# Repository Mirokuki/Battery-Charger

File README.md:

# 6-slot 1S / 2S USB-C LiPo balance charger

A USB-C powered charger with six independent slots. Every slot takes either a
1S pack (PicoBlade, e.g. Blade Nano 150 mAh) or a 2S pack (XT30 plus its JST-XH
balance lead, e.g. Mobula8 350 mAh). It works out which one is plugged in and
charges it at the voltage and rate you set on a small OLED with three buttons.
2S packs are balanced while they charge, and both cell voltages are shown.

**Status: design files generated, nothing built or powered yet.** See
[Before you order](#before-you-order).

## How it works

```
USB-C ── AP33771C (asks the adapter for 9 V) ── VBUS ─┬─ AP63203 buck ── 3.3 V ── ESP32-C3, OLED, I2C mux
                                                     └─ 6 x BQ25798 buck-boost charger (one per slot)

slot:  BQ25798 BAT ──┬── P-FET pair ── PicoBlade (1S)      switch driven by the charger's D+ pin
                     └── P-FET pair ── XT30 (2S)           switch driven by the charger's D- pin
       JST-XH balance port ─┬─ BQ29209 balancer ── over-voltage flag ── charger TS pin
                            └─ 1 M dividers ── ADS1115 ADC (one per two slots) ── cell voltages
```

- **Any slot, either battery.** The BQ25798 is a buck-boost charger that is
  switched between 1S and 2S over I2C, so it also works from a plain 5 V port.
- **Detection.** With charging off, the firmware empties the charger's output
  node, closes one connector's switch and reads the pack voltage with the
  charger's own ADC, then does the same for the other connector.
  - PicoBlade 2.5–4.45 V → 1S, starts charging
  - XT30 5.0–8.9 V → 2S, starts charging
  - XT30 2.5–4.45 V → could be a 1S pack or a flat 2S: asks you to confirm
  - both connectors live → fault, nothing is charged
- **The two power connectors of a slot can never be joined.** Each has its own
  back-to-back P-FET pair, off by default, and the firmware closes one at a time.
  A reverse-polarity pack cannot turn its switch on.
- **Balancing.** Each slot's JST-XH port feeds a BQ29209, which compares the
  two cells and bleeds the higher one (about 10 mA) until they match. It starts
  when the cells differ by about 30 mV and needs no firmware. It keeps working
  after the charge finishes for as long as the balance lead is plugged in.
- **Cell voltages.** Precision dividers on each balance port feed three
  ADS1115 16-bit ADCs, so the display shows both cells of a 2S pack
  (`4.12/4.15`). While charging, the firmware stops the slot if a cell goes
  more than 80 mV over the target (`cell high`), in LiHV mode too.
- **Per-cell over-voltage cut-off.** If either cell passes 4.30 V the balancer
  pulls the charger's TS pin low, which stops charging in hardware; the display
  shows `cell>4.3`. The cut-off is ignored in LiHV mode, where 4.35 V per cell
  is the target.
- **Fail-safe.** Charge-enable is pulled off in hardware, so a reset or crashed
  MCU stops all charging. The chargers' own over-voltage protection and 5 h
  safety timer stay active.
- **Power sharing.** The Samsung 25 W adapter gives about 20 W at 9 V. Six 2S
  350 mAh packs at 1C need about 18 W. If you ask for more than the adapter
  has, the firmware scales every slot down by the same factor, and each charger
  also backs off by itself if the input voltage sags.

### Limits you should know about

- **Balancing is gentle.** At about 10 mA it corrects roughly 10 mAh per
  hour, which suits packs that are slightly out, not badly unbalanced ones.
  The balancer runs by itself; the firmware watches the cells but does not
  steer it.
- **A forgotten balance lead is not blocked.** A 2S pack on the XT30 alone
  still charges, unbalanced and without any per-cell protection. You can tell
  from the display: it shows one pack voltage instead of two cell voltages.
- **Cell readings are good to about 10 mV** with the 0.1 % divider resistors
  in the BOM. With 1 % parts expect up to about 40 mV of error.
- **Small packs stop a little early.** The charger chip's lowest termination
  current is 40 mA. For 150 mAh packs the firmware adds a 15 minute top-off,
  but expect roughly 95 % rather than a full 100 %.
- **LiPo vs LiHV cannot be detected**, so it is a per-slot setting (default
  4.20 V, which is safe for both).
- "Storage" only charges up to 3.85 V/cell. It cannot discharge a fuller pack.
- Charge rate is 50–1000 mA per slot in 10 mA steps. Current accuracy near the
  bottom of that range is modest (the chip is a 5 A design).

## Using it

2S: plug in the balance lead and the XT30. 1S: plug into the PicoBlade.

Each slot has one line on the main screen. A 2S pack with its balance lead
shows `2S 4.12/4.15` (cell 1 / cell 2) and the charge current; a balance lead
on its own shows `bal 4.12/4.15`, which makes the charger a quick cell checker.

| Button | Main screen | Slot menu |
|---|---|---|
| UP / DN | pick a slot | move, or change a value while editing |
| OK | open the slot menu | edit / confirm / run the item |

Slot menu: 1S voltage, 1S rate, 2S voltage, 2S rate, Start/Stop, Back. Settings
are remembered per slot. Defaults are 150 mA for 1S and 350 mA for 2S. The green
LED under each slot is on while that slot charges.

Hold **OK** while plugging in USB to put the ESP32 into download mode.

## Files

| Path | What |
|---|---|
| `hardware/design.py` | The circuit: every part, value, order code and net. Edit this, then regenerate. |
| `hardware/gen_schematic.py` | Writes the KiCad schematic (`lipo-charger.kicad_sch`, `slot1..6.kicad_sch`). |
| `hardware/gen_pcb.py` | Places and routes the 108 x 80 mm 4-layer board (`lipo-charger.kicad_pcb`). |
| `hardware/make_outputs.py` | Gerbers, drill, BOM, pick-and-place, schematic PDF, DRC/ERC reports. |
| `hardware/render_copper.py` | Quick picture of the routed copper (`docs/copper.png`). |
| `fab/` | What you upload to JLCPCB. |
| `firmware/lipo_charger/` | Arduino sketch for the ESP32-C3. |
| `case/make_case.py` | Generates `case_base.stl` and `case_lid.stl`. |
| `docs/` | Schematic PDF and board renders. |

Regenerate everything:

```
python hardware/gen_schematic.py
"C:\Program Files\KiCad\10.0\bin\python.exe" hardware/gen_pcb.py
python hardware/make_outputs.py
python case/make_case.py
```

The schematic uses a net label on every pin instead of drawn wires. It is
generated from `design.py` and checked against it, so it is exact, but it reads
like a netlist rather than a hand-drawn schematic.

## Ordering the board (JLCPCB)

- Upload `fab/lipo-charger-gerbers.zip`: 4 layers, 1.6 mm, 1 oz.
- SMT assembly, top side only: `fab/BOM_JLCPCB.csv` and `fab/CPL_JLCPCB.csv`.
  Every surface-mount part is on the top; the bottom carries only copper.
- Rows in the BOM with an empty LCSC number need to be matched by MPN in
  JLCPCB's parts search. The LCSC numbers that are filled in were entered from
  memory and **must be checked** against the part description when you upload.
- Check part rotations in JLCPCB's placement preview, especially the BQ25798,
  the BQ29209, the ADS1115s, the SOT-23 FETs, the LEDs and the ESP32 module.

Hand-soldered after delivery: 6 x XT30UPB-M, 6 x JST B3B-XH-A, 6 x PicoBlade
53047-0210, the OLED module on J2. J3 (UART) is optional.

The OLED is a 0.96" SSD1306 I2C module with pins in the order **GND VCC SCL
SDA**. Some modules swap GND and VCC: check yours against the silkscreen. Solder
it on a plain pin header (not a socket) so the glass sits about 5.5 mm above the
board, hanging towards the front edge.

Buttons need the tall version (PTS645, 9.5 mm) to reach through the lid.

## Firmware

Arduino IDE, board **ESP32C3 Dev Module**, *USB CDC On Boot: Enabled*.
Libraries: Adafruit GFX, Adafruit SSD1306. Flash over the USB-C port.

## Case

Outside size 112.8 x 84.8 x 14.8 mm. `case_base.stl` prints as is,
`case_lid.stl` is already flipped to print top-face down. No supports.

Hardware: 4 x M3 heat-set insert (5.0 mm knurl, 4.2 mm pilot, 4.0 mm long) and
4 x M3 x 8 socket-head screw.

1. Melt an insert into the open end of each of the four lid posts, flush with
   the end of the post.
2. Drop the board into the base. It rests on the four bosses and seven pegs.
3. Fit the lid. The posts land on the board around its M3 holes.
4. Screw in from underneath. The heads sit in 6.2 x 3.2 mm recesses, so the
   case sits flat, and the top of the lid has no screw holes.

The opening sizes, insert hole (`INSERT_HOLE`, 4.2 mm) and screw recess are
parameters at the top of `case/make_case.py`. Print one post as a test before
committing to the insert hole size for your filament. The OLED window position
(`OLED_WIN`) depends on the module, so measure yours first.

## Before you order

Nothing here has been built. Do these first:

1. **Open the board in KiCad and look it over.** It was placed and routed by
   script. Rule-check results are in the section below.
2. **PicoBlade polarity.** Pin 1 (the pad nearer the balance port) is positive,
   pin 2 is ground. Check with a meter that this matches your Blade packs. A
   reversed pack is simply not detected, so a wrong guess shows up as "nothing
   happens", not damage.
3. **Balance port pinout.** Pin 1 (square pad, at the left) is pack negative,
   pin 2 the cell junction, pin 3 pack positive, which is the usual JST-XH
   balance wiring. Check one of your packs with a meter.
4. **The D+/D- switch drive is unusual.** The BQ25798 documents its D+/D-
   pins as host-programmable 0–3.3 V outputs (register 0x47), and this design
   uses them to drive the FET gate drivers. The datasheet does not state how
   much current they source; the load here is 49 µA. Worth proving on one slot
   before populating all six.
5. **Order the BQ29209, not the BQ29200.** The two share a datasheet; the
   BQ29209 trips at 4.30 V per cell, the BQ29200 at 4.35 V.
6. **First power-up without batteries**, on a current-limited supply if you
   have one. All six slots should report `--`. Then try one pack with a meter
   on it and compare voltage and current with the display.
7. **Compile the firmware.** It has not been compiled or run.
8. Never leave charging packs unattended, especially on an unproven charger.

## Rule-check results

From the last run on 2026-11-11 (KiCad 10.0, `hardware/make_outputs.py`):

| Check | Result |
|---|---|
| Schematic netlist vs `design.py` | 397 of 397 parts, 0 net mismatches |
| Board vs schematic (parity) | 0 issues |
| Board DRC errors | 0 |
| Unconnected nets | 0 |
| Board DRC warnings | 9: seven unused escape vias on I2C lines, two silkscreen lines of the ESP32 module at the board edge |
| Schematic ERC | 3 "power pin not driven" (the schematic has no power-flag symbols) and 7 library notes about generated symbols. No wiring faults. |
| Case meshes | both STLs closed (every edge shared by exactly two faces) |

Board rules used: 0.127 mm clearance, 0.15 mm minimum track, 0.6/0.3 mm vias,
0.2 mm minimum hole (the ESP32 footprint's thermal vias), 0.18 mm hole clearance
(the USB-C footprint's own locating holes sit 0.194 mm from its pads).

DRC proves the copper matches the netlist and meets spacing rules. It does not
prove the circuit works: see "Before you order".

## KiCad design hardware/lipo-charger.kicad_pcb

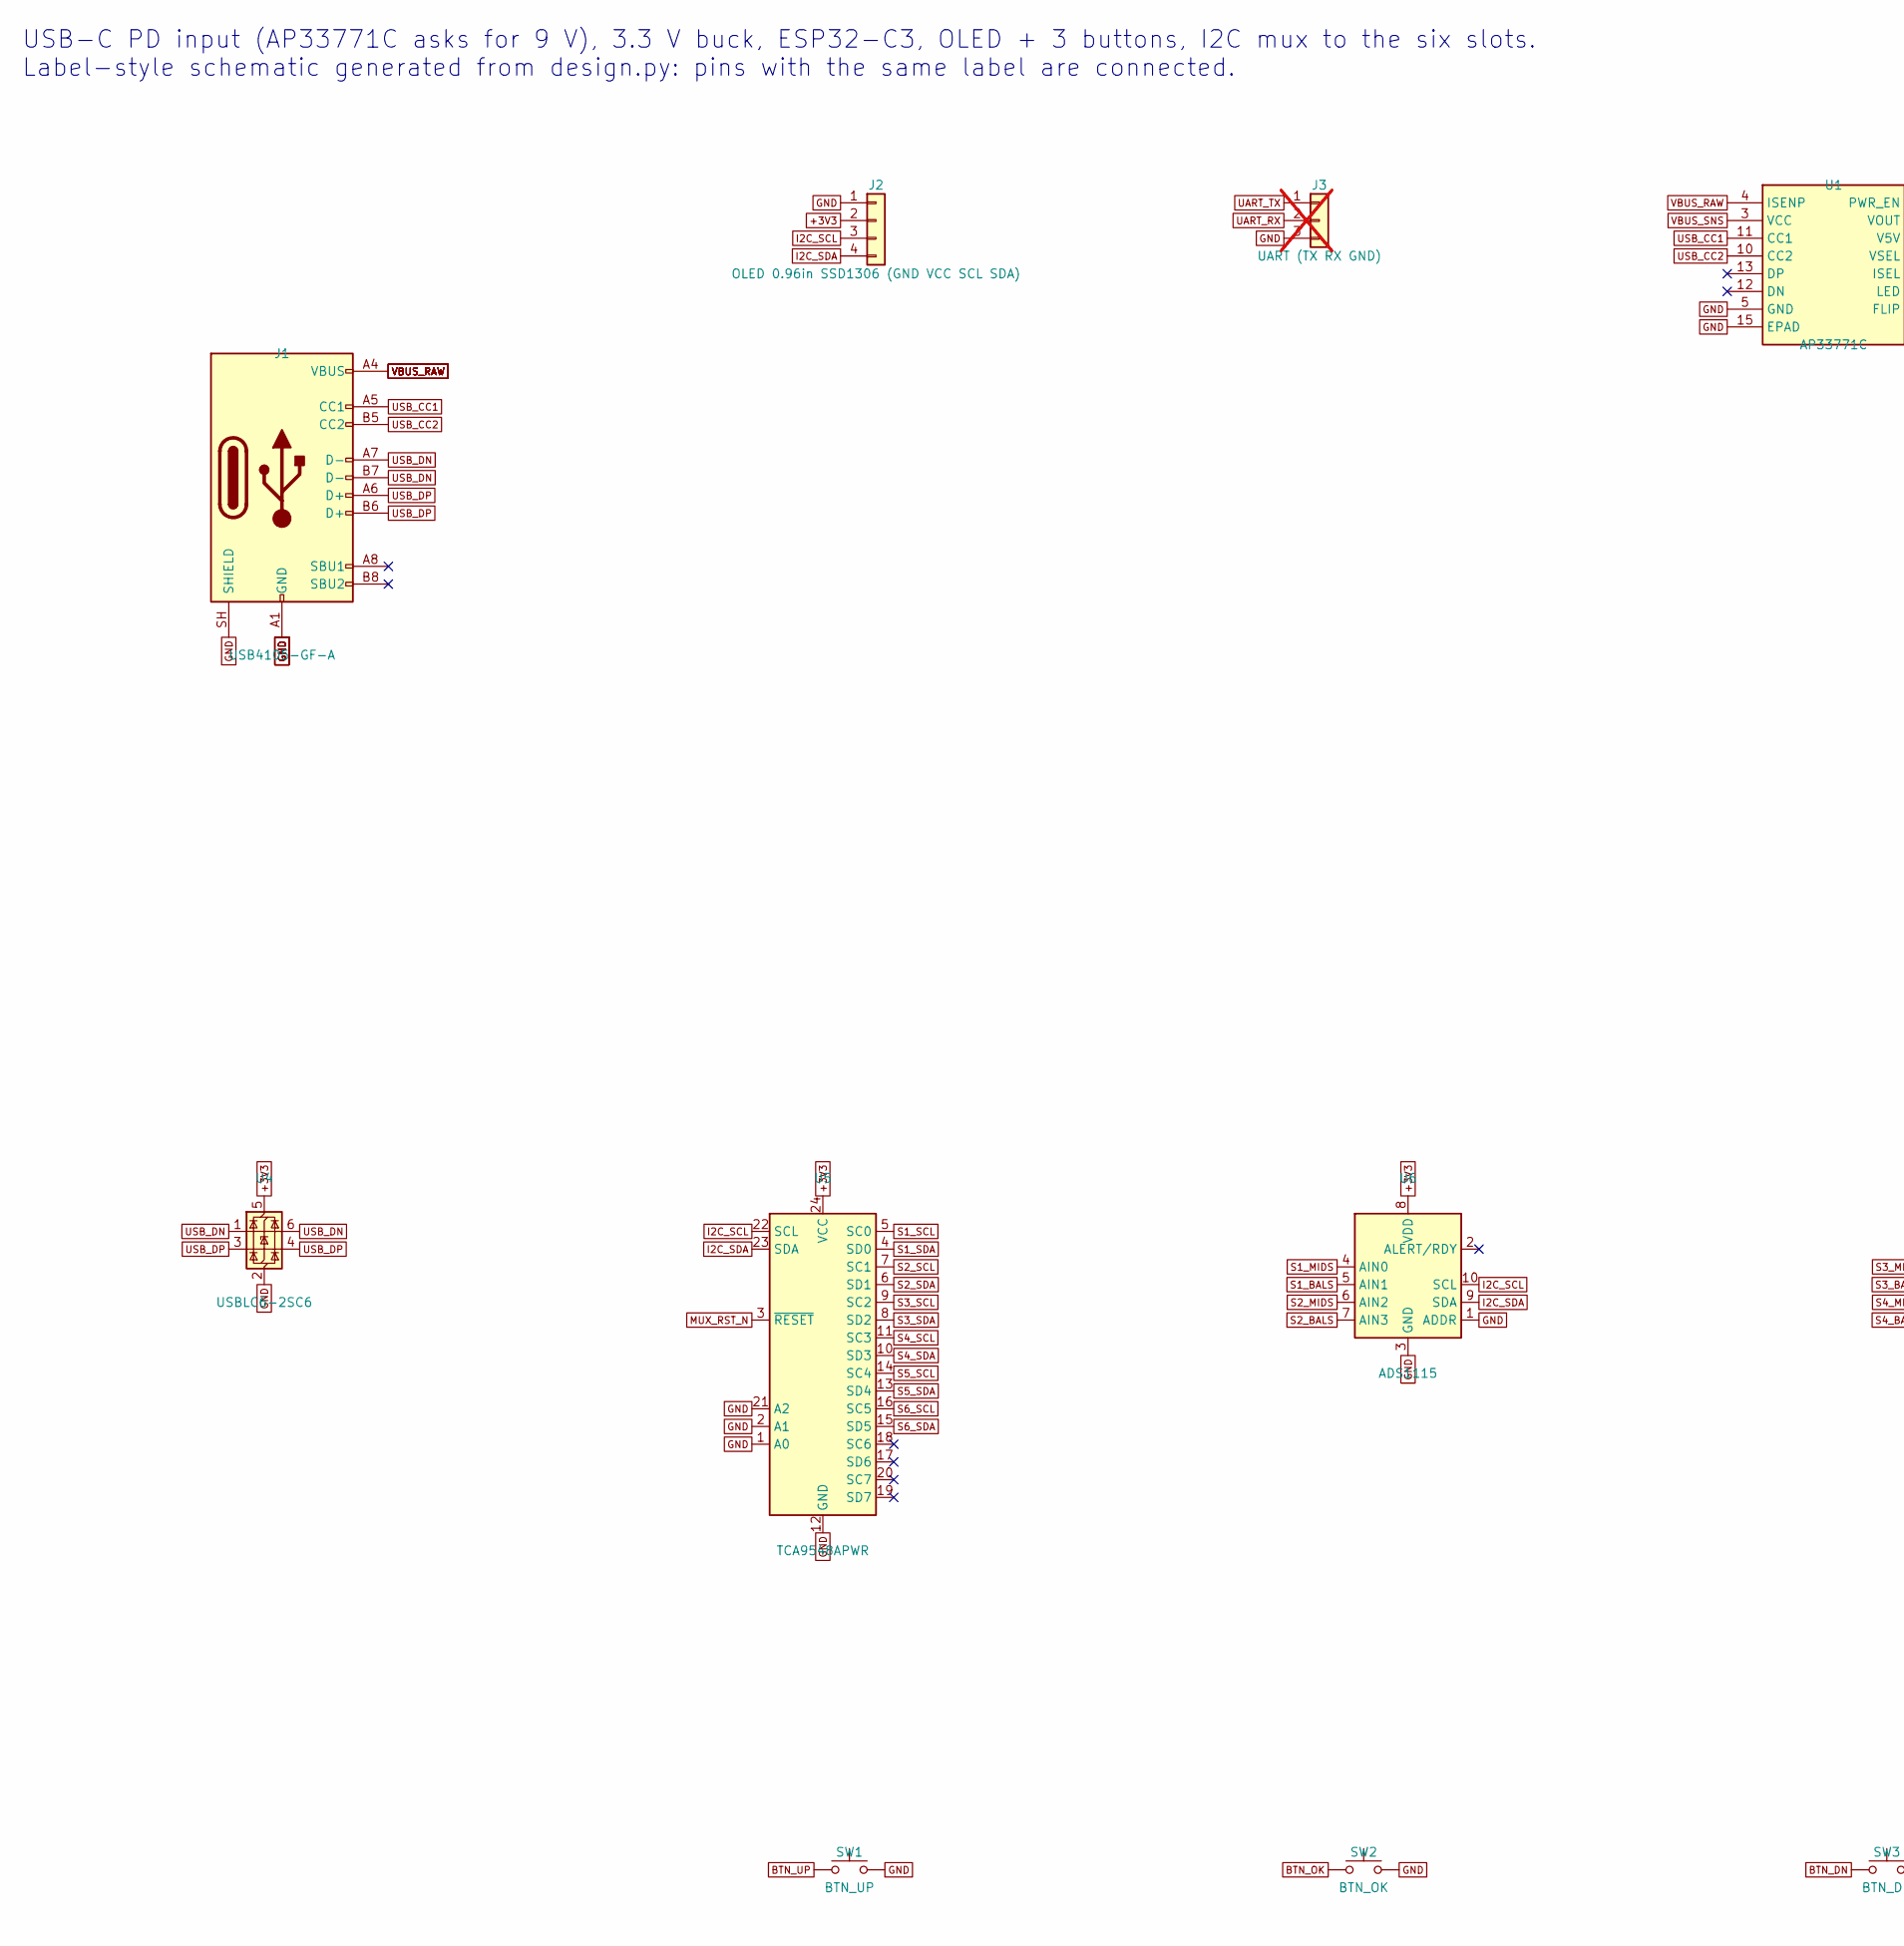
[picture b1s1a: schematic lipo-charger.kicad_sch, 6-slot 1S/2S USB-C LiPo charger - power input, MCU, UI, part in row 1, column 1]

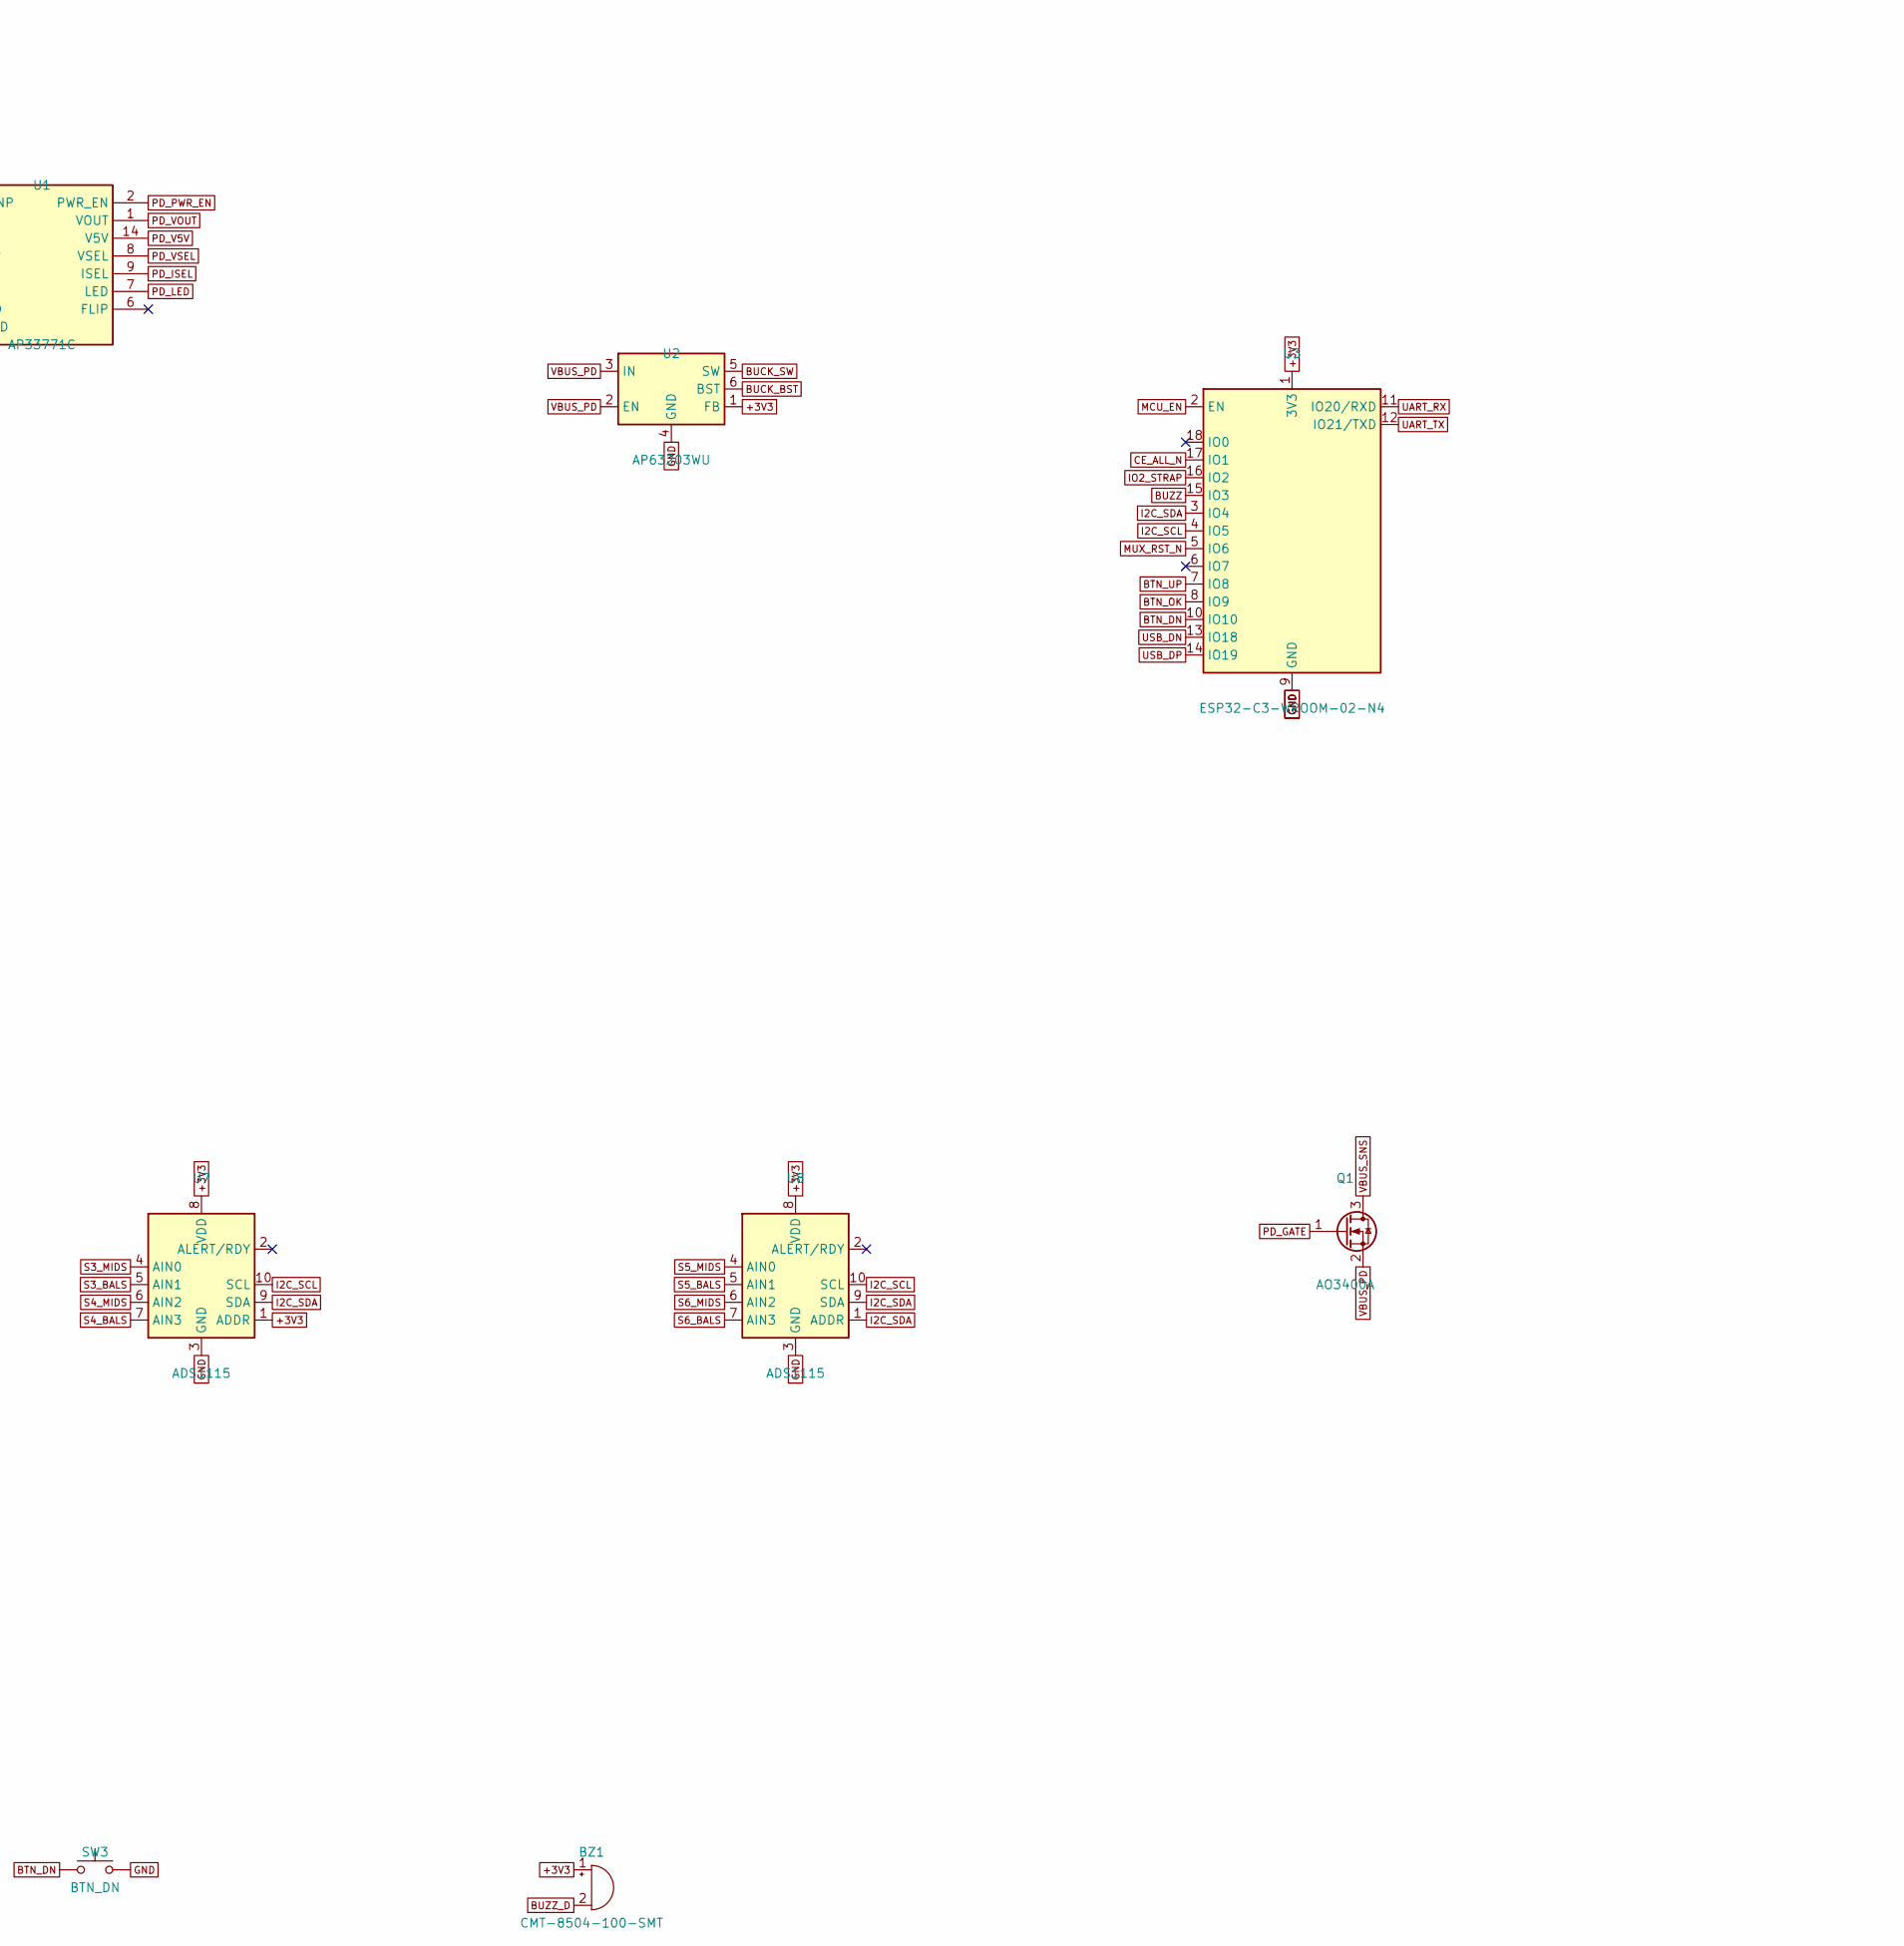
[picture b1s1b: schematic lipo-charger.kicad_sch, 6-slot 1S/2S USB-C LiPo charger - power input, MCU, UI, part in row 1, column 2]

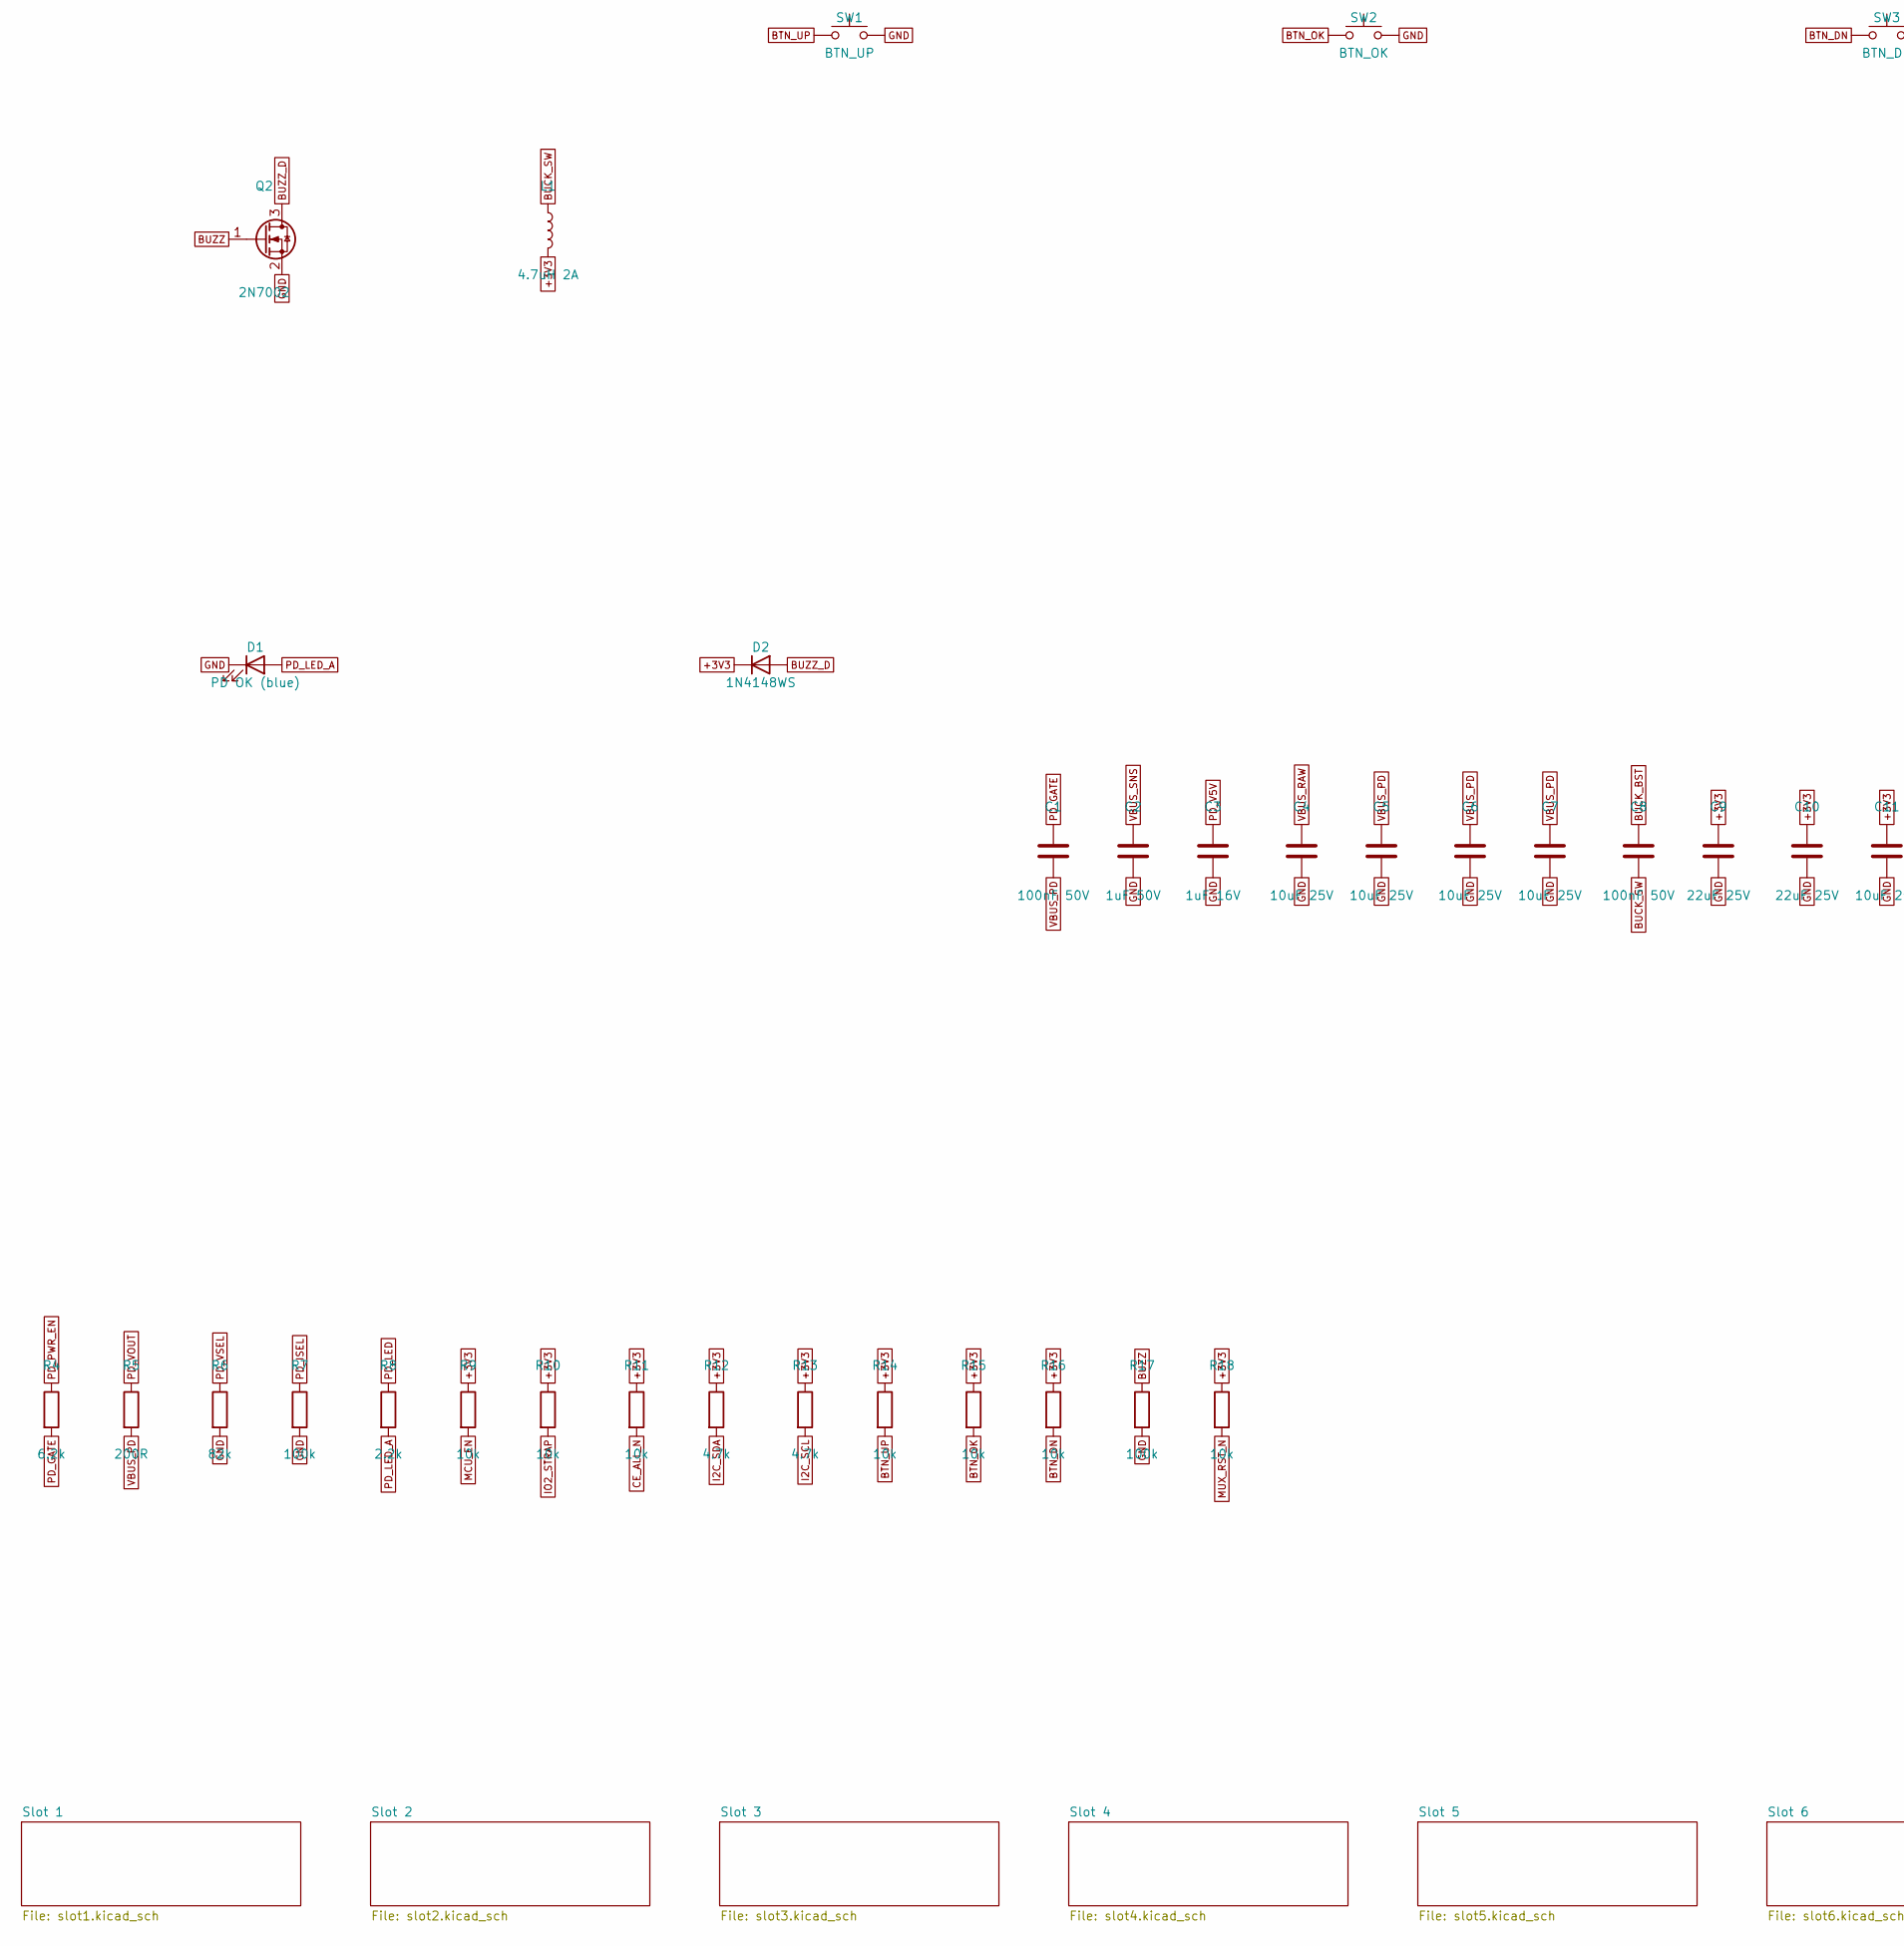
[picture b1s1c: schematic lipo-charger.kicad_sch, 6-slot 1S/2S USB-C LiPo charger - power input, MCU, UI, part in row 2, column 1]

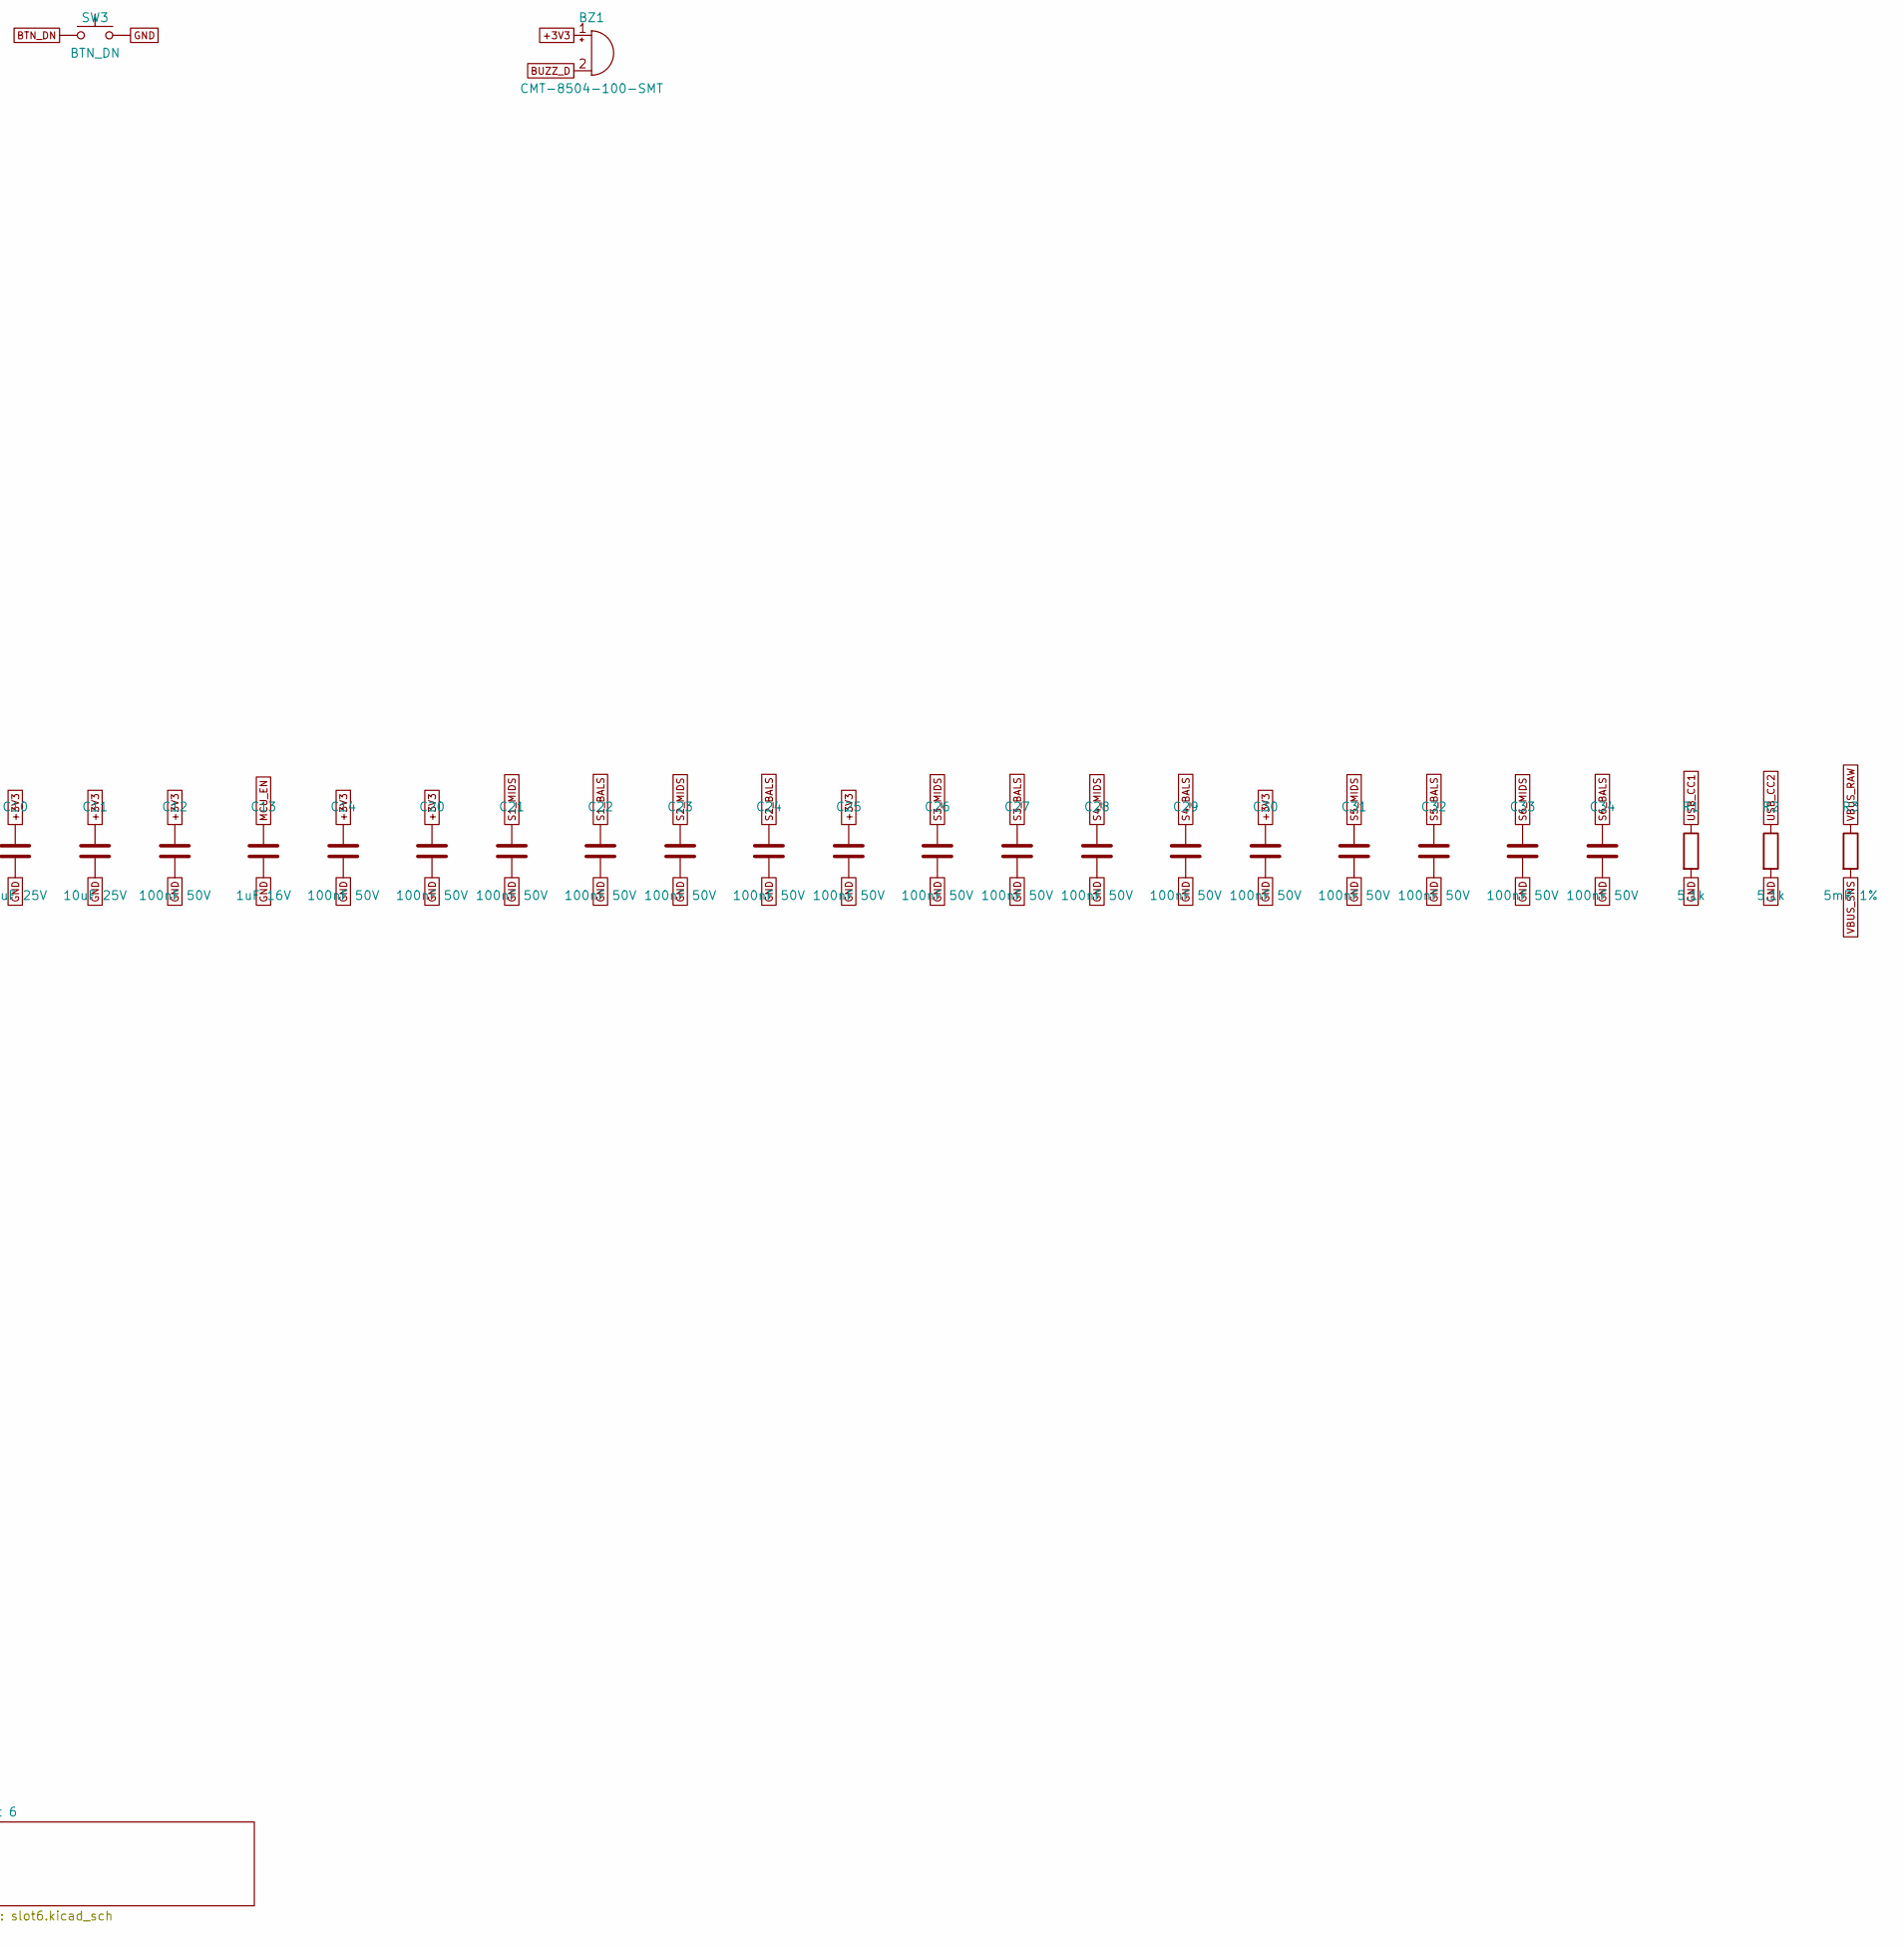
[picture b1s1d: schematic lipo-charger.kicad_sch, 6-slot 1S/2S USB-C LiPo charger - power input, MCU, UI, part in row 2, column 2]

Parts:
BZ1: CMT-8504-100-SMT; MagneticBuzzer_CUI_CMT-8504-100-SMT; MPN CMT-8504-100-SMT-TR
C1, C8, C12, C14, C20, C21, C22, C23, C24, C25, C26, C27, C28, C29, C30, C31, C32, C33, C34: 100nF 50V; C_0402_1005Metric; MPN CL05B104KB54PNC; LCSC C307331
C2: 1uF 50V; C_0603_1608Metric; MPN CL10A105KB8NNNC; LCSC C15849
C3, C13: 1uF 16V; C_0402_1005Metric; MPN CL05A105KA5NQNC; LCSC C52923
C4, C5, C6, C7, C11: 10uF 25V; C_0805_2012Metric; MPN CL21A106KAYNNNE; LCSC C15850
C9, C10: 22uF 25V; C_0805_2012Metric; MPN CL21A226MAQNNNE; LCSC C45783
D1: PD OK (blue); LED_0603_1608Metric; MPN 19-217/BHC-ZL1M2RY/3T; LCSC C72041
D2: 1N4148WS; D_SOD-323; MPN 1N4148WS; LCSC C2128
J1: USB4105-GF-A; USB_C_Receptacle_GCT_USB4105-xx-A_16P_TopMnt_Horizontal; MPN USB4105-GF-A; LCSC C3020560
J2: OLED 0.96in SSD1306 (GND VCC SCL SDA); PinHeader_1x04_P2.54mm_Vertical
J3: UART (TX RX GND); PinHeader_1x03_P2.54mm_Vertical; not fitted
L1: 4.7uH 2A; L_Changjiang_FNR4030S; MPN FNR4030S4R7MT
Q1: AO3400A; SOT-23; MPN AO3400A; LCSC C20917
Q2: 2N7002; SOT-23; MPN 2N7002; LCSC C8545
R1, R2: 5.1k; R_0402_1005Metric; MPN 0402WGF5101TCE; LCSC C25905
R3: 5mR 1%; R_1206_3216Metric; MPN PE1206FKF470R005Z
R4: 6.2k; R_0402_1005Metric; MPN 0402WGF6201TCE
R5: 200R; R_0402_1005Metric; MPN 0402WGF2000TCE; LCSC C25087
R6: 82k; R_0402_1005Metric; MPN 0402WGF8202TCE; LCSC C25958
R7, R17: 100k; R_0402_1005Metric; MPN 0402WGF1003TCE; LCSC C25741
R8: 2.2k; R_0402_1005Metric; MPN 0402WGF2201TCE; LCSC C25879
R9, R10, R11, R14, R15, R16, R18: 10k; R_0402_1005Metric; MPN 0402WGF1002TCE; LCSC C25744
R12, R13: 4.7k; R_0402_1005Metric; MPN 0402WGF4701TCE; LCSC C25900
SW1: BTN_UP; SW_SPST_PTS645Sx43SMTR92; MPN PTS645SM95SMTR92 LFS
SW2: BTN_OK; SW_SPST_PTS645Sx43SMTR92; MPN PTS645SM95SMTR92 LFS
SW3: BTN_DN; SW_SPST_PTS645Sx43SMTR92; MPN PTS645SM95SMTR92 LFS
U1: AP33771C; DFN-14-1EP_3x3mm_P0.4mm_EP1.78x2.35mm; MPN AP33771CFBZ-13-FA02
U2: AP63203WU; TSOT-23-6; MPN AP63203WU-7; LCSC C780769
U3: ESP32-C3-WROOM-02-N4; ESP32-C3-WROOM-02; MPN ESP32-C3-WROOM-02-N4; LCSC C2934560
U4: USBLC6-2SC6; SOT-23-6; MPN USBLC6-2SC6; LCSC C7519
U5: TCA9548APWR; TSSOP-24_4.4x7.8mm_P0.65mm; MPN TCA9548APWR; LCSC C130026
U6, U7, U8: ADS1115; TSSOP-10_3x3mm_P0.5mm; MPN ADS1115IDGSR; LCSC C37593

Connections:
+3V3: BZ1.1 (+), C9.1, C10.1, C11.1, C12.1, C14.1, C20.1, C25.1, C30.1, D2.1 (K), J2.2, L1.2, R9.1, R10.1, R11.1, R12.1, R13.1, R14.1, R15.1, R16.1, R18.1, U2.1 (FB), U3.1 (3V3), U4.5 (VBUS), U5.24 (VCC), U6.8 (VDD), U7.1 (ADDR), U7.8 (VDD), U8.8 (VDD); also elsewhere on the board
BTN_DN: R16.2, SW3.1, U3.10 (IO10)
BTN_OK: R15.2, SW2.1, U3.8 (IO9)
BTN_UP: R14.2, SW1.1, U3.7 (IO8)
BUCK_BST: C8.1, U2.6 (BST)
BUCK_SW: C8.2, L1.1, U2.5 (SW)
BUZZ: Q2.1 (G), R17.1, U3.15 (IO3)
BUZZ_D: BZ1.2 (-), D2.2 (A), Q2.3 (D)
CE_ALL_N: R11.2, U3.17 (IO1); also elsewhere on the board
GND: C2.2, C3.2, C4.2, C5.2, C6.2, C7.2, C9.2, C10.2, C11.2, C12.2, C13.2, C14.2, C20.2, C21.2, C22.2, C23.2, C24.2, C25.2, C26.2, C27.2, C28.2, C29.2, C30.2, C31.2, C32.2, C33.2, C34.2, D1.1 (K), J1.A1 (GND), J1.A12 (GND), J1.B1 (GND), J1.B12 (GND), J1.SH (SHIELD), J2.1, J3.3, Q2.2 (S), R1.2, R2.2, R6.2, R7.2, R17.2, SW1.2, SW2.2, SW3.2, U1.5 (GND), U1.15 (EPAD), U2.4 (GND), U3.9 (GND), U3.19 (GND), U4.2 (GND), U5.1 (A0), U5.2 (A1), U5.12 (GND), U5.21 (A2), U6.1 (ADDR), U6.3 (GND), U7.3 (GND), U8.3 (GND); also elsewhere on the board
I2C_SCL: J2.3, R13.2, U3.4 (IO5), U5.22 (SCL), U6.10 (SCL), U7.10 (SCL), U8.10 (SCL)
I2C_SDA: J2.4, R12.2, U3.3 (IO4), U5.23 (SDA), U6.9 (SDA), U7.9 (SDA), U8.1 (ADDR), U8.9 (SDA)
IO2_STRAP: R10.2, U3.16 (IO2)
MCU_EN: C13.1, R9.2, U3.2 (EN)
MUX_RST_N: R18.2, U3.5 (IO6), U5.3 (~RESET)
PD_GATE: C1.1, Q1.1 (G), R4.2
PD_ISEL: R7.1, U1.9 (ISEL)
PD_LED: R8.1, U1.7 (LED)
PD_LED_A: D1.2 (A), R8.2
PD_PWR_EN: R4.1, U1.2 (PWR_EN)
PD_V5V: C3.1, U1.14 (V5V)
PD_VOUT: R5.1, U1.1 (VOUT)
PD_VSEL: R6.1, U1.8 (VSEL)
S1_BALS: C22.1, U6.5 (AIN1); also elsewhere on the board
S1_MIDS: C21.1, U6.4 (AIN0); also elsewhere on the board
S1_SCL: U5.5 (SC0); also elsewhere on the board
S1_SDA: U5.4 (SD0); also elsewhere on the board
S2_BALS: C24.1, U6.7 (AIN3); also elsewhere on the board
S2_MIDS: C23.1, U6.6 (AIN2); also elsewhere on the board
S2_SCL: U5.7 (SC1); also elsewhere on the board
S2_SDA: U5.6 (SD1); also elsewhere on the board
S3_BALS: C27.1, U7.5 (AIN1); also elsewhere on the board
S3_MIDS: C26.1, U7.4 (AIN0); also elsewhere on the board
S3_SCL: U5.9 (SC2); also elsewhere on the board
S3_SDA: U5.8 (SD2); also elsewhere on the board
S4_BALS: C29.1, U7.7 (AIN3); also elsewhere on the board
S4_MIDS: C28.1, U7.6 (AIN2); also elsewhere on the board
S4_SCL: U5.11 (SC3); also elsewhere on the board
S4_SDA: U5.10 (SD3); also elsewhere on the board
S5_BALS: C32.1, U8.5 (AIN1); also elsewhere on the board
S5_MIDS: C31.1, U8.4 (AIN0); also elsewhere on the board
S5_SCL: U5.14 (SC4); also elsewhere on the board
S5_SDA: U5.13 (SD4); also elsewhere on the board
S6_BALS: C34.1, U8.7 (AIN3); also elsewhere on the board
S6_MIDS: C33.1, U8.6 (AIN2); also elsewhere on the board
S6_SCL: U5.16 (SC5); also elsewhere on the board
S6_SDA: U5.15 (SD5); also elsewhere on the board
UART_RX: J3.2, U3.11 (IO20/RXD)
UART_TX: J3.1, U3.12 (IO21/TXD)
USB_CC1: J1.A5 (CC1), R1.1, U1.11 (CC1)
USB_CC2: J1.B5 (CC2), R2.1, U1.10 (CC2)
USB_DN: J1.A7 (D-), J1.B7 (D-), U3.13 (IO18), U4.1 (I/O1), U4.6 (I/O1)
USB_DP: J1.A6 (D+), J1.B6 (D+), U3.14 (IO19), U4.3 (I/O2), U4.4 (I/O2)
VBUS_PD: C1.2, C5.1, C6.1, C7.1, Q1.2 (S), R5.2, U2.2 (EN), U2.3 (IN); also elsewhere on the board
VBUS_RAW: C4.1, J1.A4 (VBUS), J1.A9 (VBUS), J1.B4 (VBUS), J1.B9 (VBUS), R3.1, U1.4 (ISENP)
VBUS_SNS: C2.1, Q1.3 (D), R3.2, U1.3 (VCC)

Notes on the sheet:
USB-C PD input (AP33771C asks for 9 V), 3.3 V buck, ESP32-C3, OLED + 3 buttons, I2C mux to the six slots. Label-style schematic generated from design.py: pins with the same label are connected.
